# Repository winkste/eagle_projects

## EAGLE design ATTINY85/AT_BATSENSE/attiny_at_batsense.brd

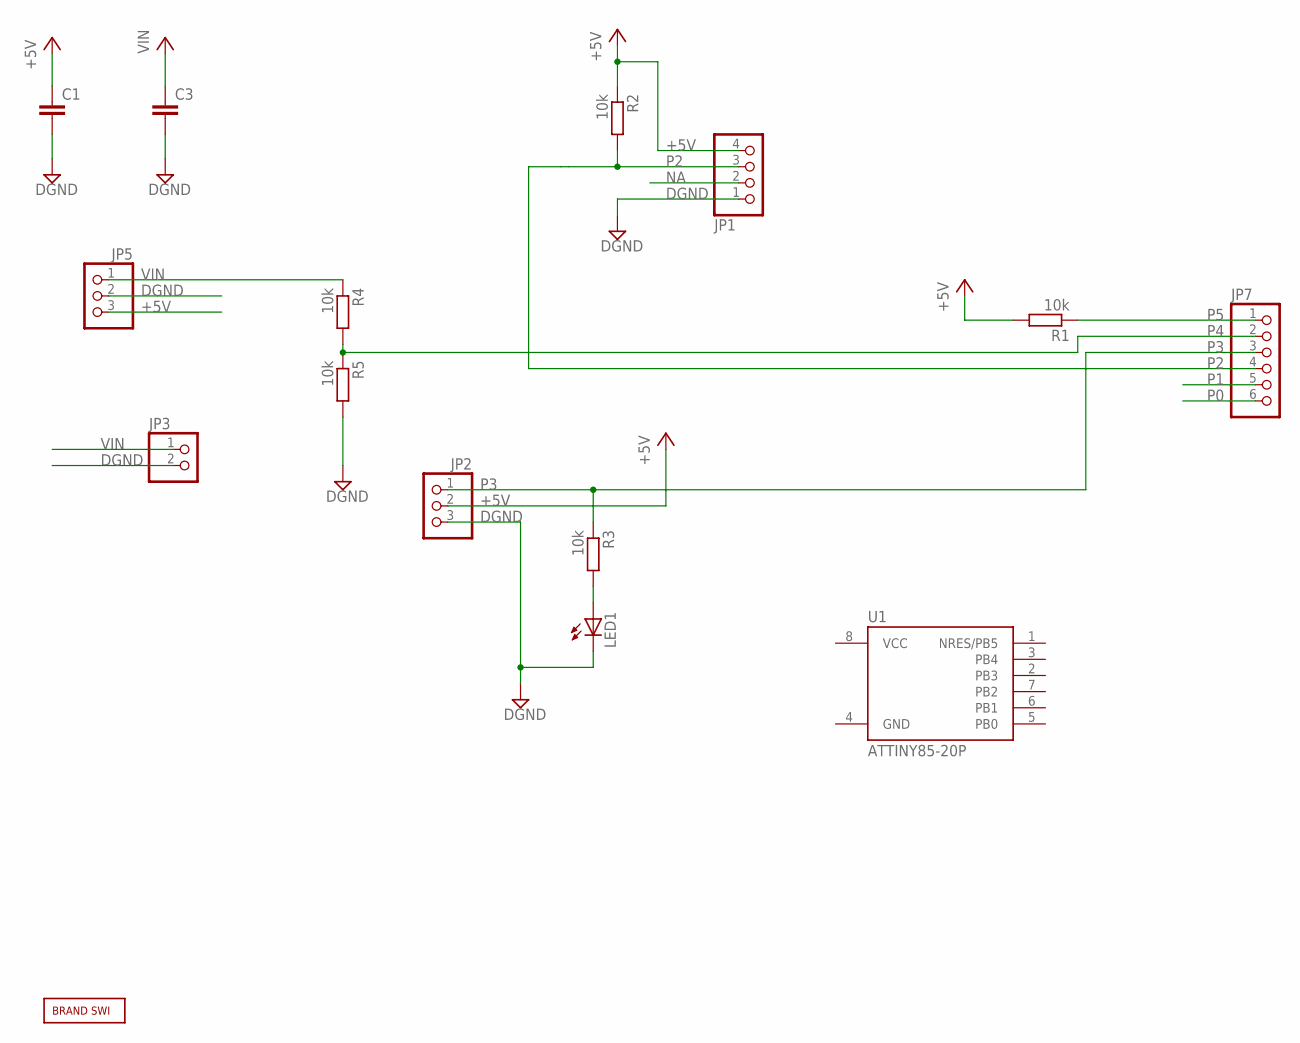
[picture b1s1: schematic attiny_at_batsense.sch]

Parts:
C1, C3: C-EUC1210; C1210
JP1: PINHD-1X4; 1X04
JP2, JP5: PINHD-1X3; 1X03
JP3: PINHD-1X2; 1X02
JP7: PINHD-1X6; 1X06
LED1: LED3MM
R1, R2, R3, R4, R5: 10k; R0805
U1: ATTINY85-20P; PDIP08_300MIL
U$2: BRAND_SWI5X7; BRAND_SWI_5X7

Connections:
+5V: C1.1, JP1.4, JP2.2, JP5.3, R1.2, R2.1
DGND: C1.2, C3.2, JP1.1, JP2.3, JP3.2, JP5.2, LED1.K (C), R5.2
GND: U1.4 (GND)
unnamed: LED1.A, R3.2
NA: JP1.2
P0: JP7.6
P1: JP7.5
P2: JP1.3, JP7.4, R2.2
P3: JP2.1, JP7.3, R3.1
P4: JP7.2, R4.2, R5.1
P5: JP7.1, R1.1
VIN: C3.1, JP3.1, JP5.1, R4.1, U1.8 (VCC)

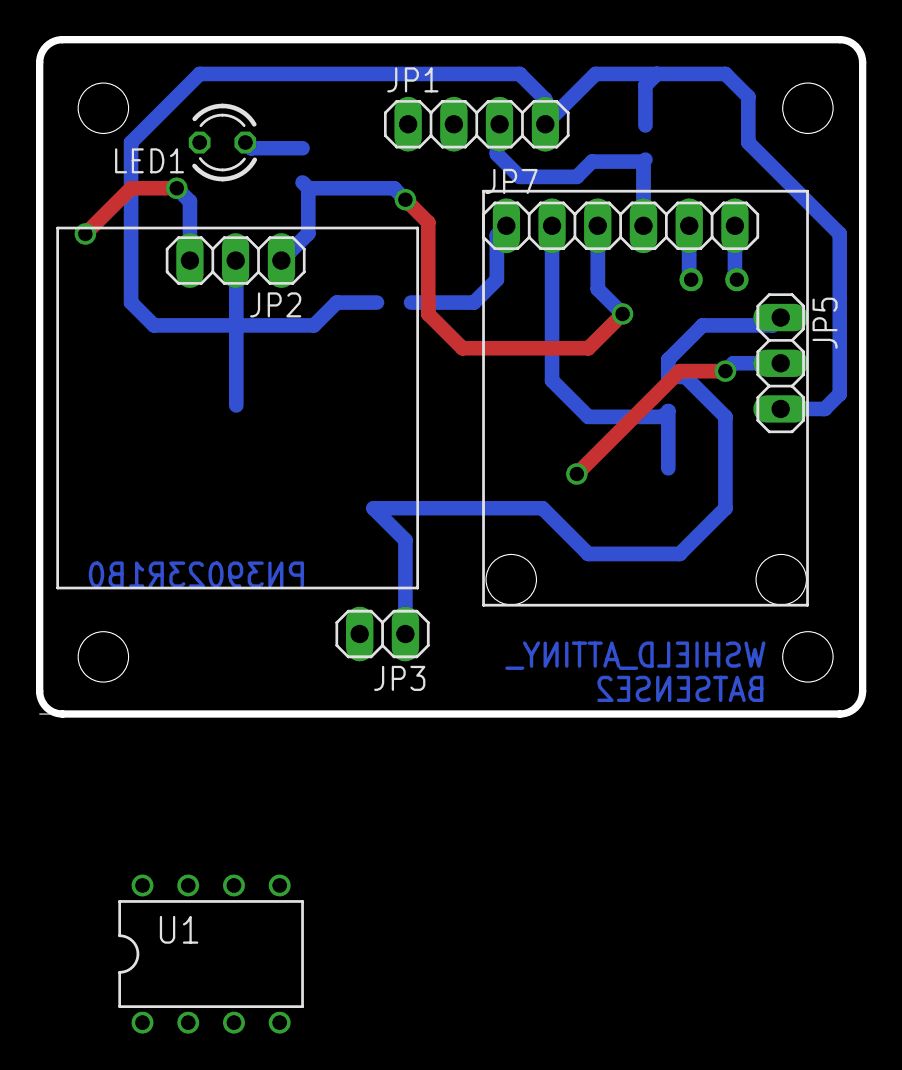
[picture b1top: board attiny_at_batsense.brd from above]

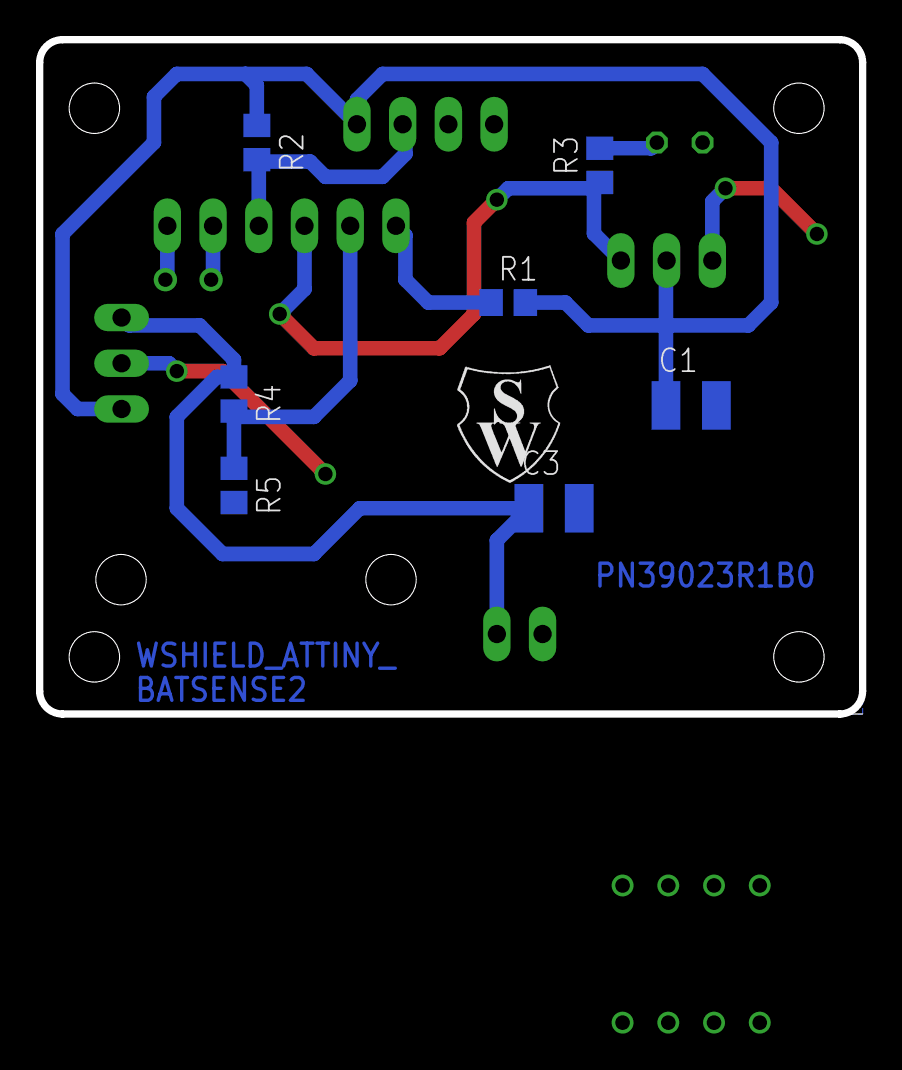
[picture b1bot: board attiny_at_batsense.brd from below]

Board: 2 copper layers, 45.7 x 37.5 mm, 15 parts (8 on the bottom side), 8 nets.

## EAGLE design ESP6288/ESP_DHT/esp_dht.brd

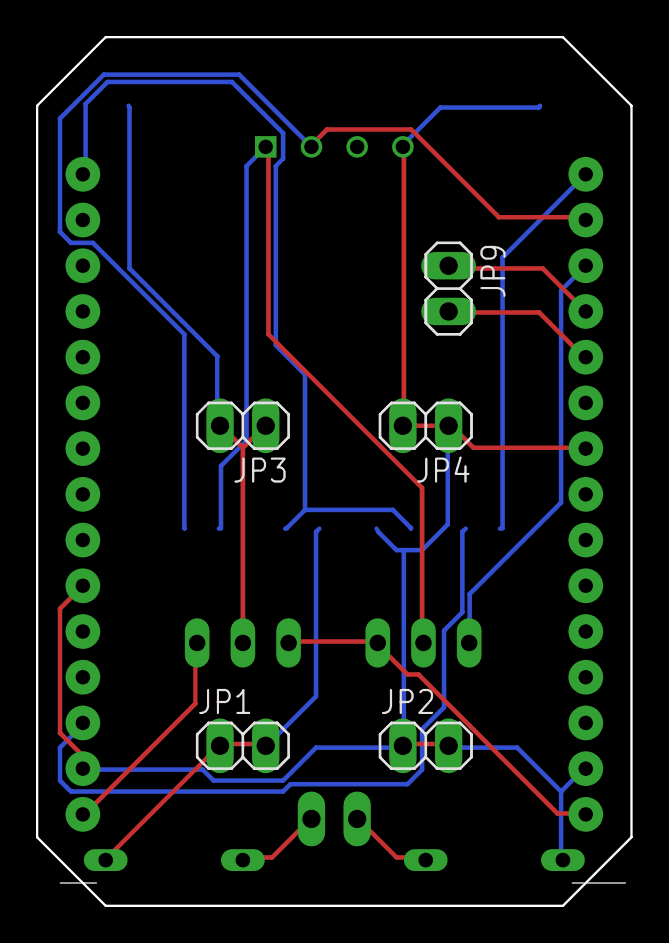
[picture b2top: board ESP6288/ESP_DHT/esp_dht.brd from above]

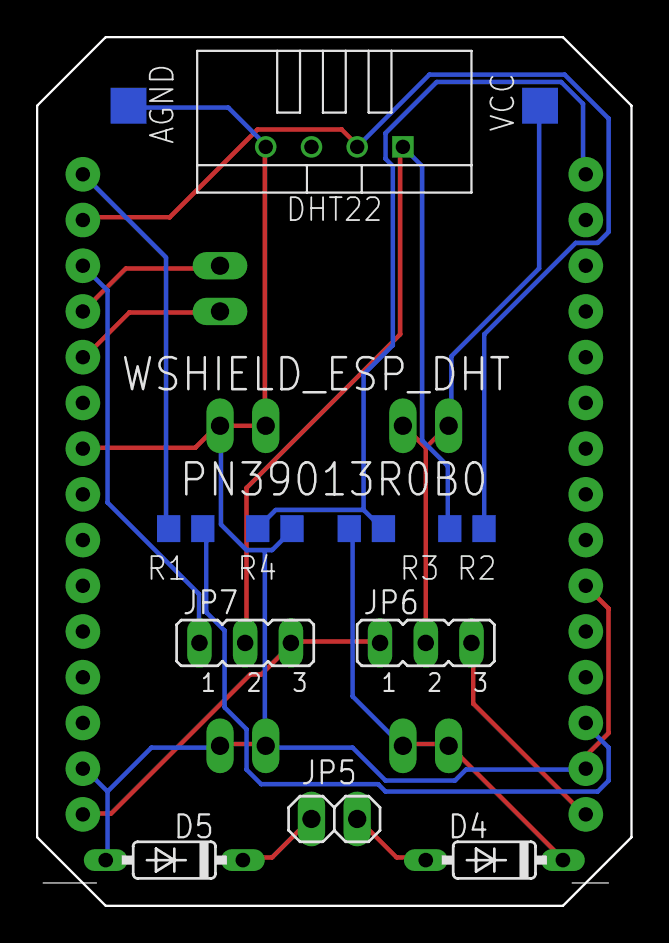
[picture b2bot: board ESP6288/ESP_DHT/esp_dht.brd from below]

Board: 2 copper layers, 33.0 x 48.3 mm, 18 parts (12 on the bottom side), 15 nets.

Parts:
AGND: TPSQTP20SQ; TP20SQ
D4, D5: 1N4148DO35-7; DO35-7
DHT22: TEMP-HUM-SENSOR-DHT22
JP1, JP2, JP3, JP4, JP5, JP9: 1X02
JP6, JP7: JP2
R1: 470Ohm; R0805
R2: 10k; R0805
R3, R4: R0805
U$3: ESP12_DEVKIT
VCC: TPSQTP20SQ; TP20SQ

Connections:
+3V3: JP6.1, JP7.3, U$3.3V3@2
+5V: JP6.3, U$3.5V
+9V: D4.C, JP1.1, JP1.2, R3.1
AGND: AGND.TP, D5.A, DHT22.4, JP2.1, JP2.2, JP4.1, JP4.2, R4.2, U$3.GND@0, U$3.GND@1, U$3.GND@2, U$3.GND@3
DHT_BUS: DHT22.2, R2.2, U$3.D1
DHT_PWR: DHT22.1, JP7.2, R2.1
unnamed: R1.1, U$3.RST
unnamed: R1.2, U$3.D0
unnamed: JP7.1, U$3.D2
unnamed: JP9.2, U$3.D4
unnamed: R3.2, R4.1, U$3.A0
unnamed: JP9.1, U$3.D3
V+: D4.A, JP5.1
V-: D5.C, JP5.2
VCC: JP3.1, JP3.2, JP6.2, VCC.TP

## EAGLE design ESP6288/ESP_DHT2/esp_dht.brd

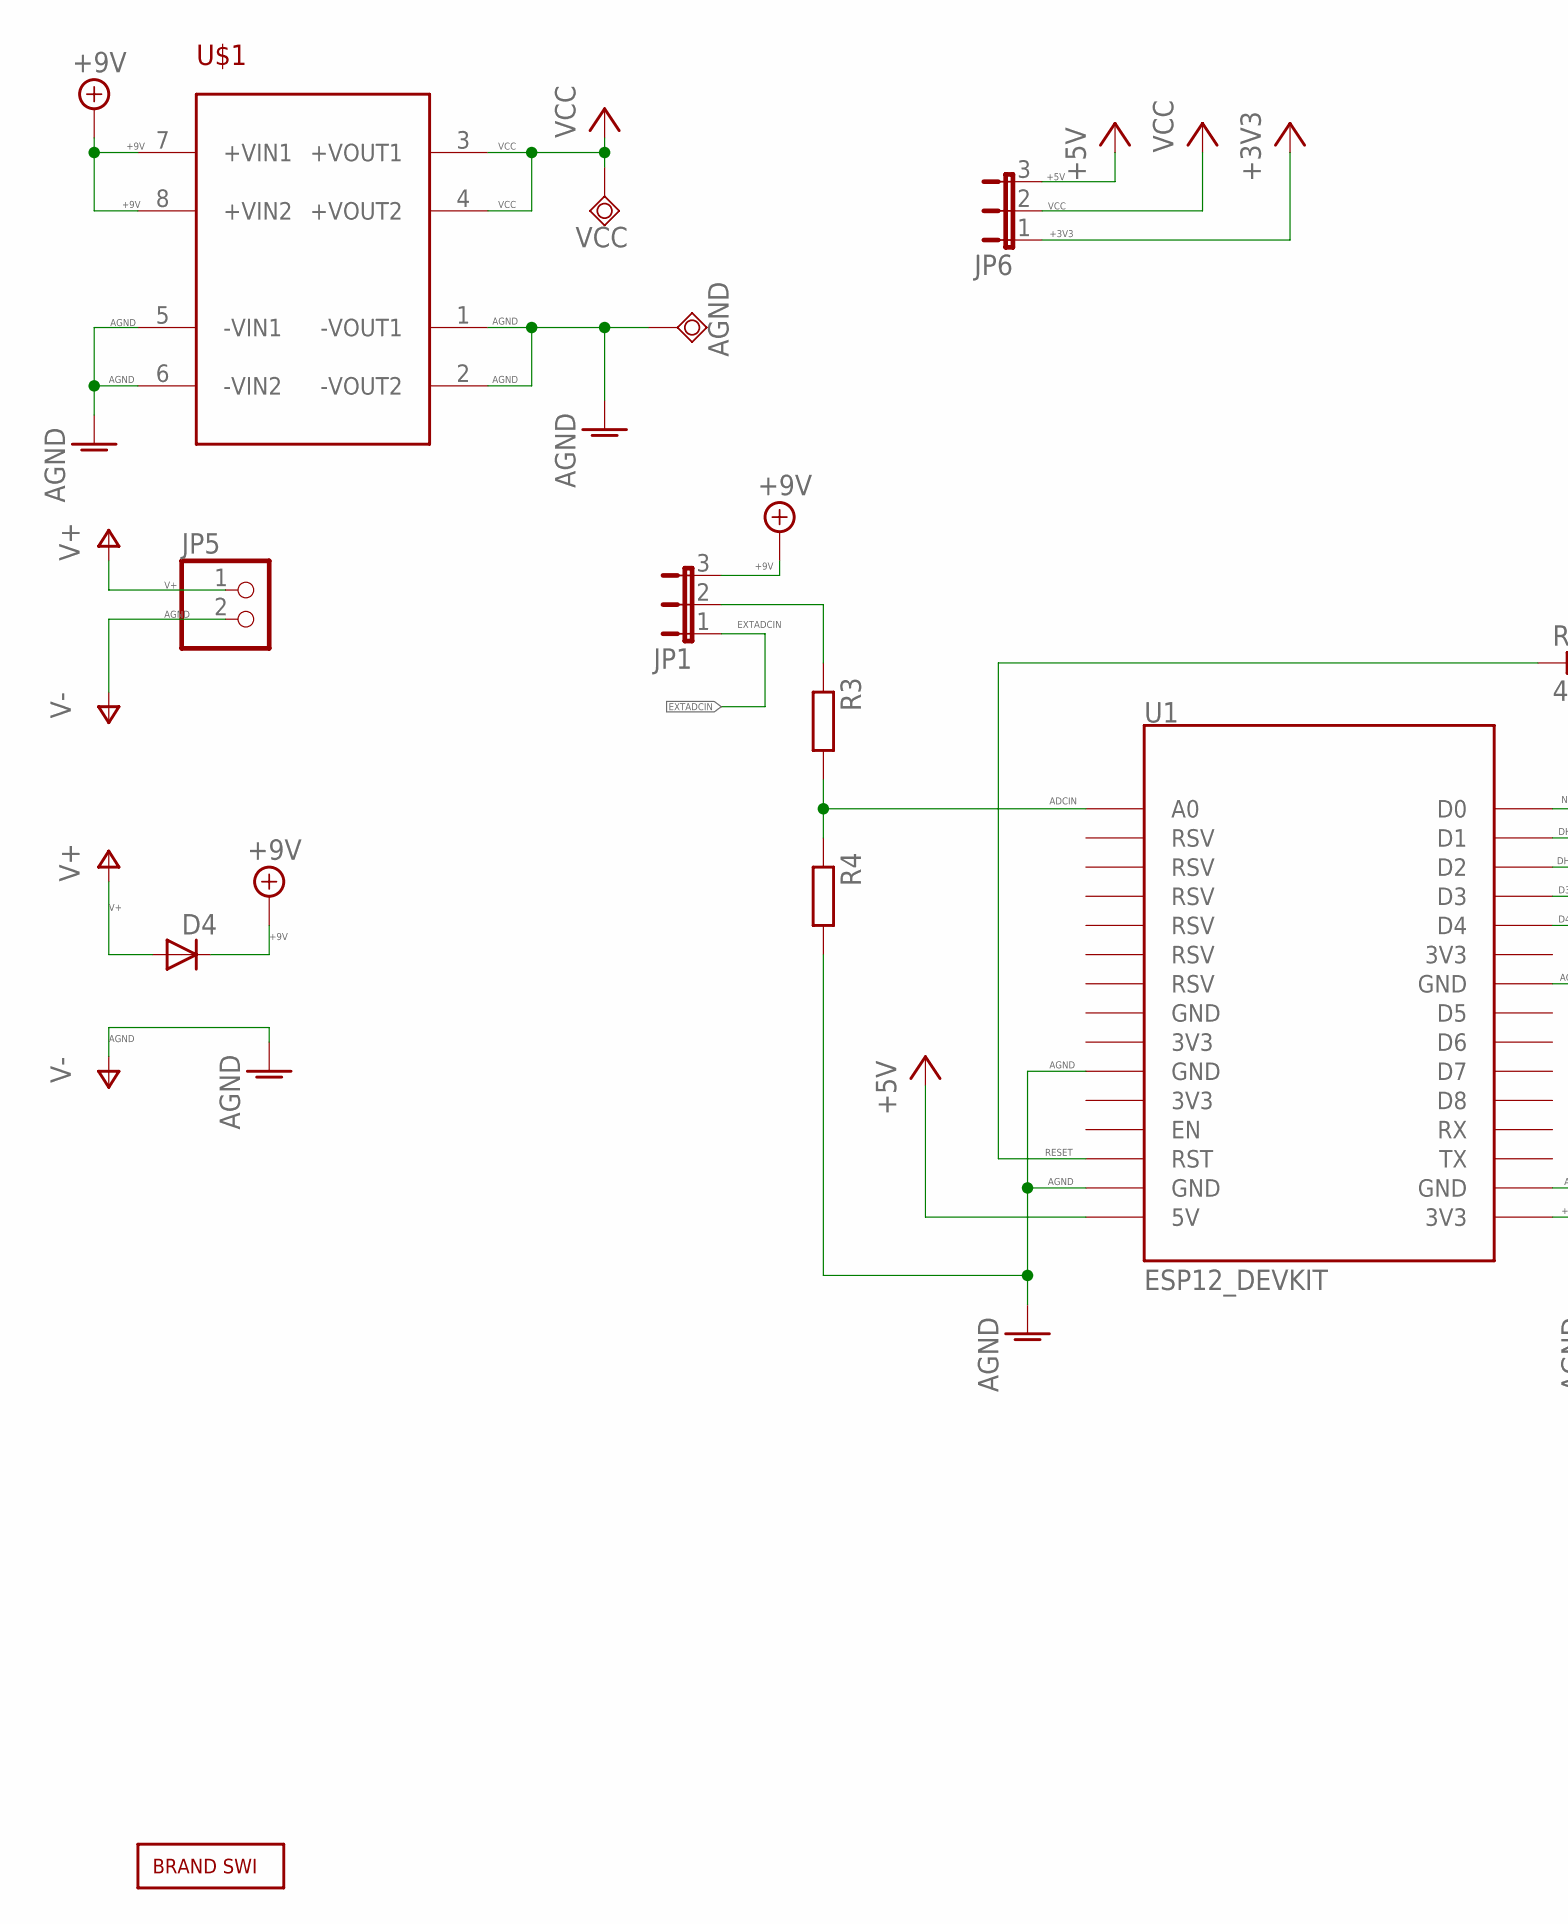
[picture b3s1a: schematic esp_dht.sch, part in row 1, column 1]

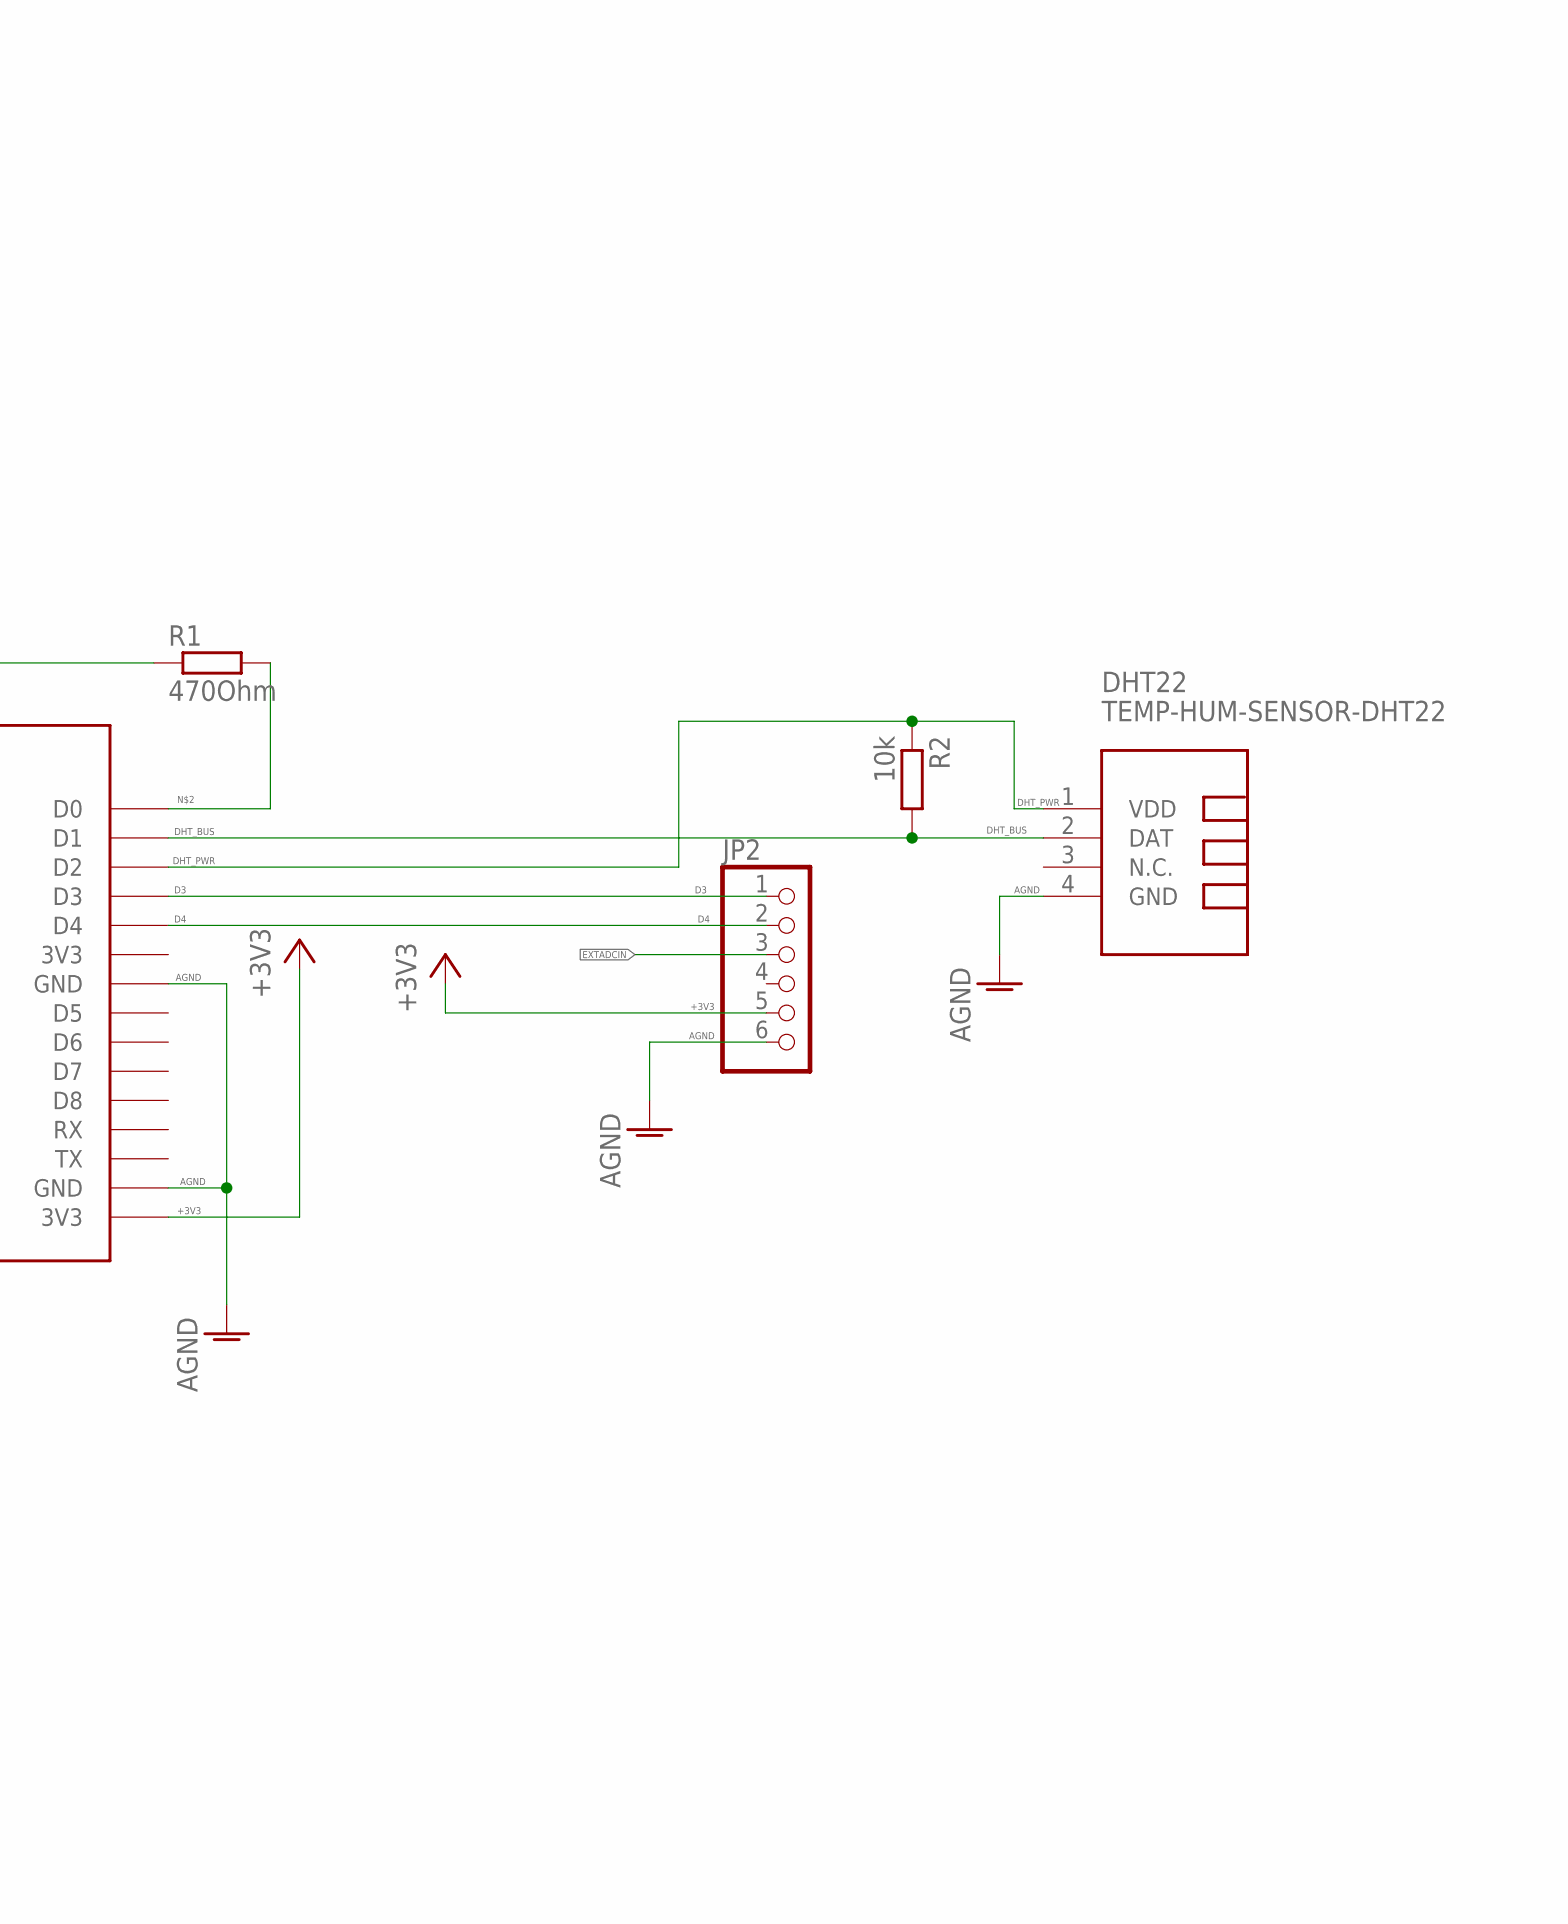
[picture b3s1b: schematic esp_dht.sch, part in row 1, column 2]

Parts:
AGND: TPSQTP20SQ; TP20SQ
D4: 1N4148DO35-7; DO35-7
DHT22: TEMP-HUM-SENSOR-DHT22
JP1, JP6: JP2E; JP2
JP2: PINHD-1X6; 1X06
JP5: PINHD-1X2; 1X02
R1: 470Ohm; R0805
R2: 10k; R0805
R3, R4: R-EU_R0805; R0805
U1: ESP12_DEVKIT
U$1: LVPS
U$2: BRAND_SWI5X7; BRAND_SWI_5X7
VCC: TPSQTP20SQ; TP20SQ

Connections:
+3V3: JP2.5, JP6.1, U1.3V3@2 (3V3)
+5V: JP6.3, U1.5V
+9V: D4.C, JP1.3, U$1.7 (+VIN1), U$1.8 (+VIN2)
ADCIN: R3.2, R4.1, U1.A0
AGND: AGND.TP, DHT22.4 (GND), JP2.6, JP5.2, R4.2, U1.GND@0 (GND), U1.GND@1 (GND), U1.GND@2 (GND), U1.GND@3 (GND), U$1.2 (-VOUT2), U$1.5 (-VIN1), U$1.6 (-VIN2)
D3: JP2.1, U1.D3
D4: JP2.2, U1.D4
DHT_BUS: DHT22.2 (DAT), R2.2, U1.D1
DHT_PWR: DHT22.1 (VDD), R2.1, U1.D2
EXTADCIN: JP1.1, JP2.3
unnamed: JP1.2, R3.1
unnamed: R1.2, U1.D0
RESET: R1.1, U1.RST
V+: D4.A, JP5.1
VCC: JP6.2, U$1.3 (+VOUT1), U$1.4 (+VOUT2), VCC.TP

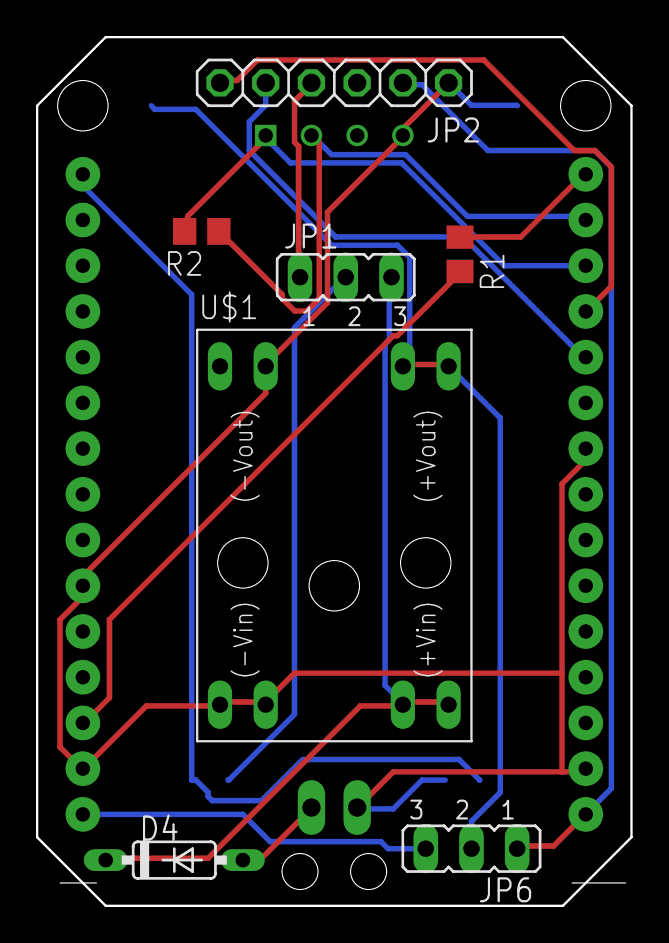
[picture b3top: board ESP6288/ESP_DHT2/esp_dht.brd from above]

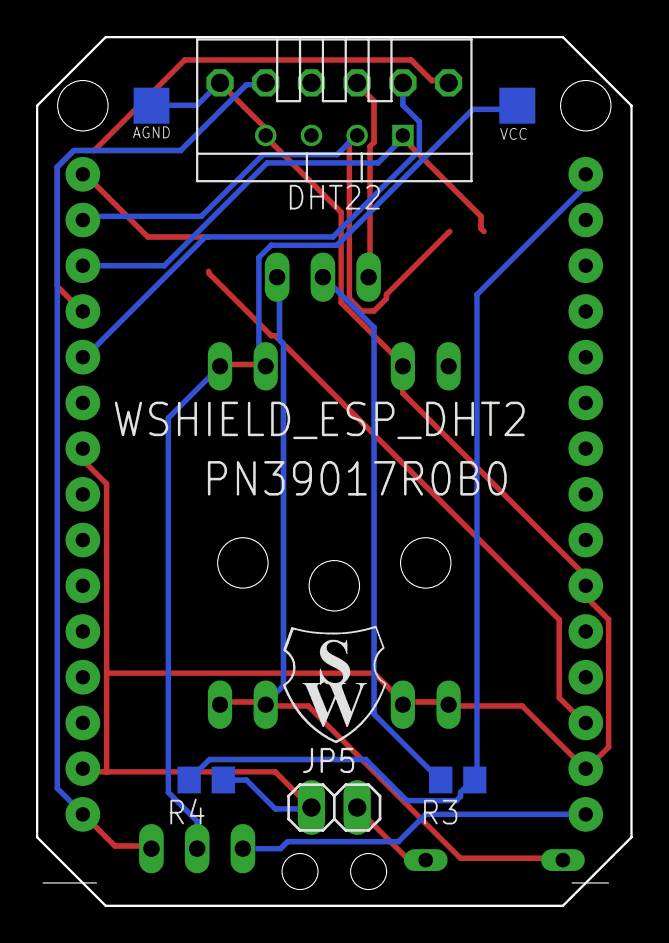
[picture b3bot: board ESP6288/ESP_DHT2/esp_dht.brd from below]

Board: 2 copper layers, 33.0 x 48.3 mm, 15 parts (7 on the bottom side), 15 nets.

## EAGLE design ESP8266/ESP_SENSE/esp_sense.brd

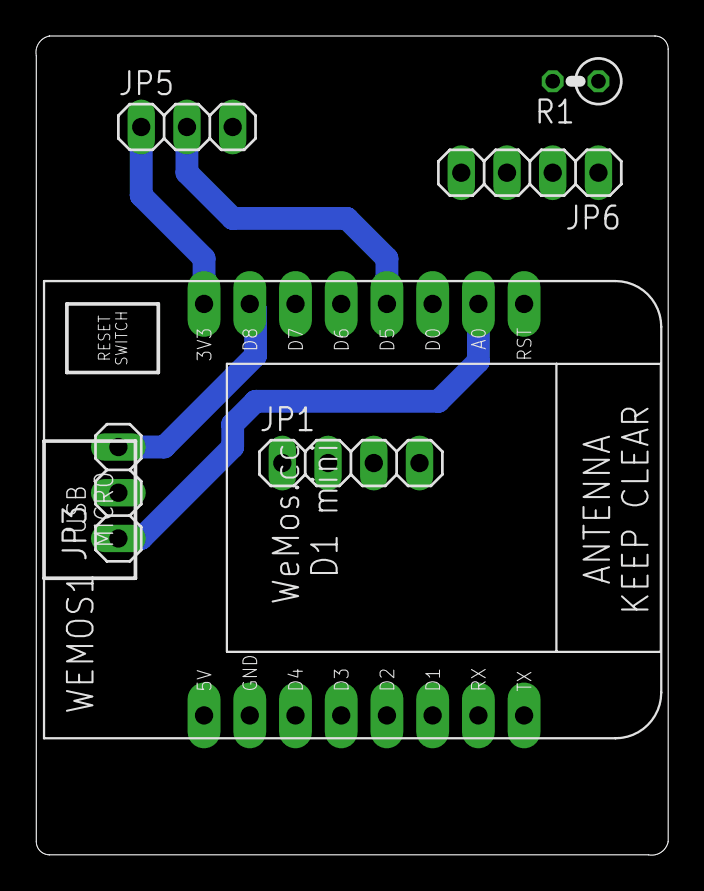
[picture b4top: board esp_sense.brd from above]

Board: 2 copper layers, 35.1 x 45.5 mm, 6 parts (0 on the bottom side), 8 nets.

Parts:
JP1, JP6: 1X04
JP3, JP5: 1X03
R1: 0207/2V
WEMOS1: WEMOS-D1-MINI

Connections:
GND: JP1.4, JP3.2, JP5.3, JP6.4, WEMOS1.GND
unnamed: JP1.1, WEMOS1.5V
unnamed: JP6.2, R1.2, WEMOS1.D3
unnamed: JP3.1, WEMOS1.A0
unnamed: JP5.2, WEMOS1.D5
unnamed: JP6.1, R1.1, WEMOS1.D7
unnamed: JP3.3, WEMOS1.D8
unnamed: JP5.1, WEMOS1.3V3

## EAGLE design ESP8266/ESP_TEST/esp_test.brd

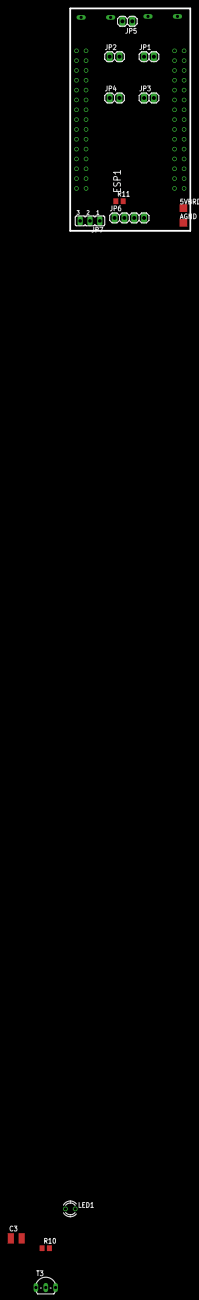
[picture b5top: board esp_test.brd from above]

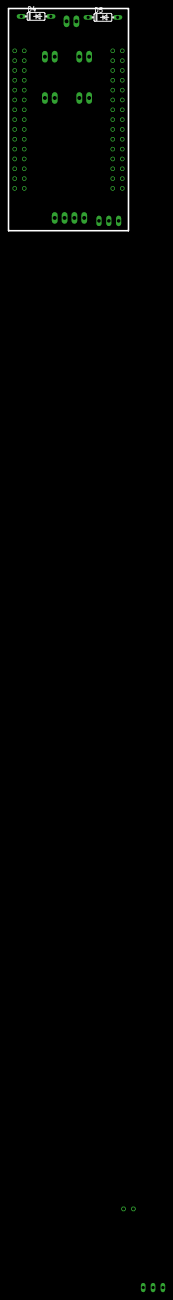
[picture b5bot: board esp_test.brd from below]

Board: 2 copper layers, 31.0 x 57.4 mm, 17 parts (2 on the bottom side), 9 nets, no tracks yet.

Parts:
5VBRD: TPSQTP20SQ; TP20SQ
AGND: TPSQTP20SQ; TP20SQ
C3: C1210
D4, D5: 1N4148DO35-7; DO35-7
ESP1: ESP12E_DEVKIT
JP1, JP2, JP3, JP4, JP5: 1X02
JP6: 1X04
JP7: JP2
LED1: LED3MM
R10: 2k; R0805
R11: R0805
T3: TO92-CBE

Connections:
+5V: 5VBRD.TP, ESP1.VIN, ESP1.VIN1, JP3.1, JP3.2, JP7.1
+9V: D4.C, JP1.1, JP1.2
AGND: AGND.TP, D5.A, ESP1.GND@0, ESP1.GND@1, ESP1.GND@2, ESP1.GND@3, ESP1.GND@4, ESP1.GND@5, ESP1.GND@6, ESP1.GND@7, JP2.1, JP2.2, JP4.1, JP4.2, JP6.4
DHT_BUS: ESP1.D4, ESP1.D41, JP6.2, R11.2
DHT_PWR: JP6.1, JP7.2, R11.1
ESP3V3: ESP1.3V3@2, JP7.3
unnamed: LED1.A, R10.2
V+: D4.A, JP5.1
V-: D5.C, JP5.2

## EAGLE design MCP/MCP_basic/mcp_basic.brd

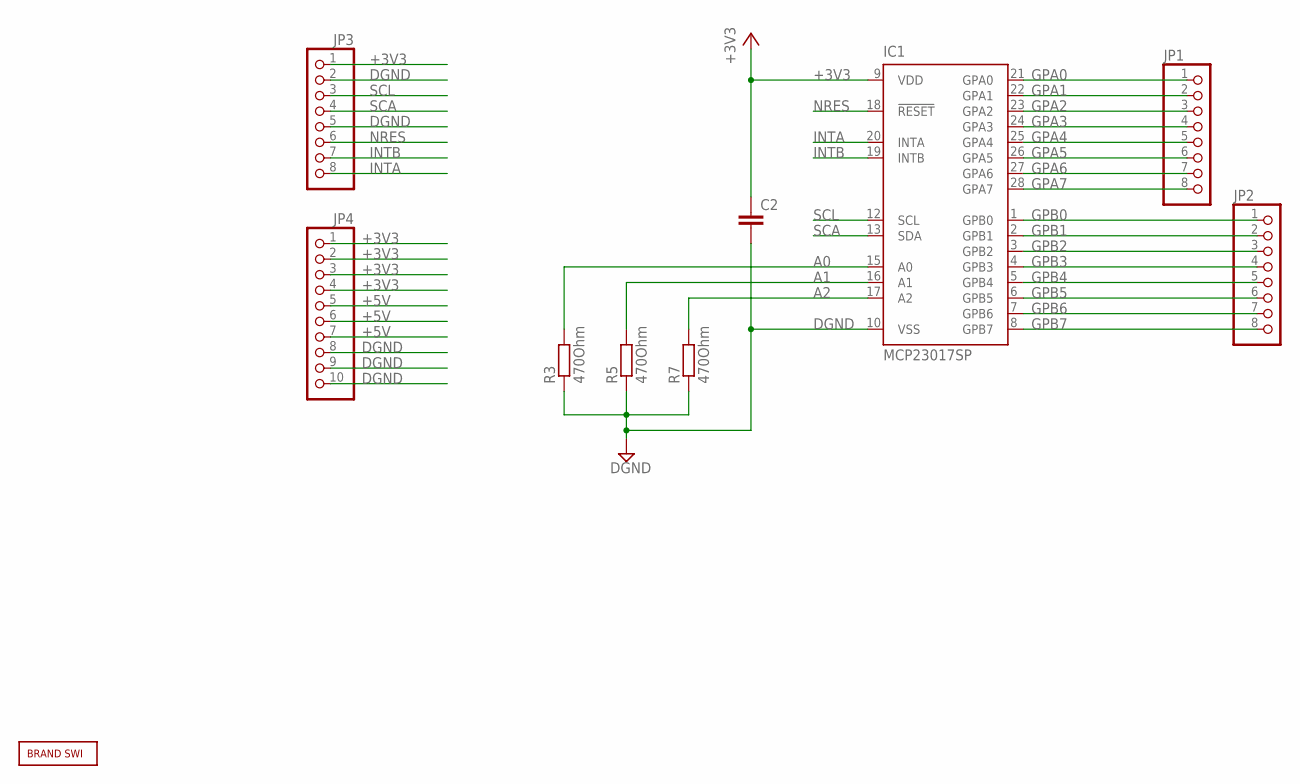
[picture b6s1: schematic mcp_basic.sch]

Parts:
C2: C-EUC1210; C1210
IC1: MCP23017SP; DIL28-3
JP1, JP2, JP3: PINHD-1X8; 1X08
JP4: PINHD-1X10; 1X10
R3, R5, R7: 470Ohm; R0805
U$2: BRAND_SWI5X7; BRAND_SWI_5X7

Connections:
+3V3: C2.1, IC1.9 (VDD), JP3.1, JP4.1, JP4.2, JP4.3, JP4.4
+5V: JP4.5, JP4.6, JP4.7
A0: IC1.15 (A0), R3.2
A1: IC1.16 (A1), R5.2
A2: IC1.17 (A2), R7.2
DGND: C2.2, IC1.10 (VSS), JP3.2, JP3.5, JP4.8, JP4.9, JP4.10, R3.1, R5.1, R7.1
GPA0: IC1.21 (GPA0), JP1.1
GPA1: IC1.22 (GPA1), JP1.2
GPA2: IC1.23 (GPA2), JP1.3
GPA3: IC1.24 (GPA3), JP1.4
GPA4: IC1.25 (GPA4), JP1.5
GPA5: IC1.26 (GPA5), JP1.6
GPA6: IC1.27 (GPA6), JP1.7
GPA7: IC1.28 (GPA7), JP1.8
GPB0: IC1.1 (GPB0), JP2.1
GPB1: IC1.2 (GPB1), JP2.2
GPB2: IC1.3 (GPB2), JP2.3
GPB3: IC1.4 (GPB3), JP2.4
GPB4: IC1.5 (GPB4), JP2.5
GPB5: IC1.6 (GPB5), JP2.6
GPB6: IC1.7 (GPB6), JP2.7
GPB7: IC1.8 (GPB7), JP2.8
INTA: IC1.20 (INTA), JP3.8
INTB: IC1.19 (INTB), JP3.7
NRES: IC1.18 (!RESET), JP3.6
SCA: IC1.13 (SDA), JP3.4
SCL: IC1.12 (SCL), JP3.3

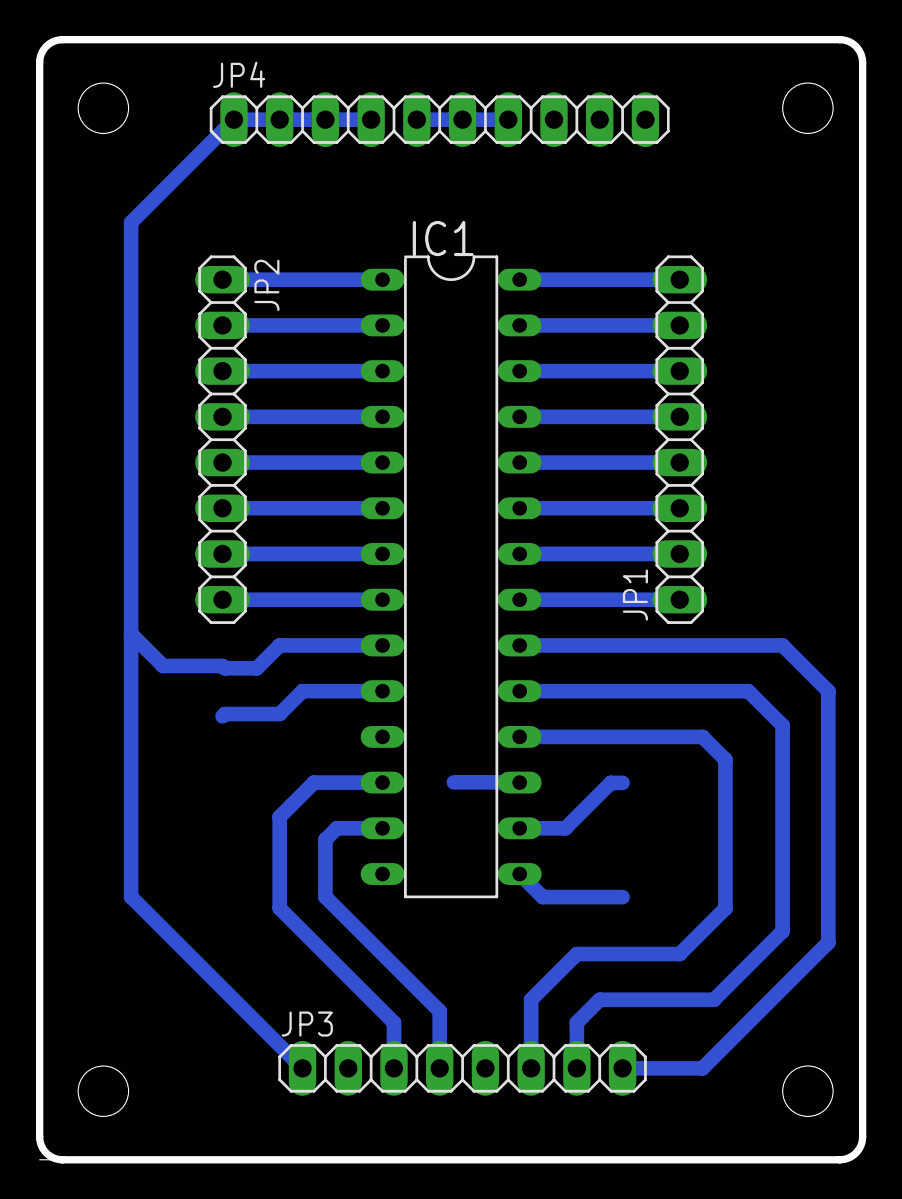
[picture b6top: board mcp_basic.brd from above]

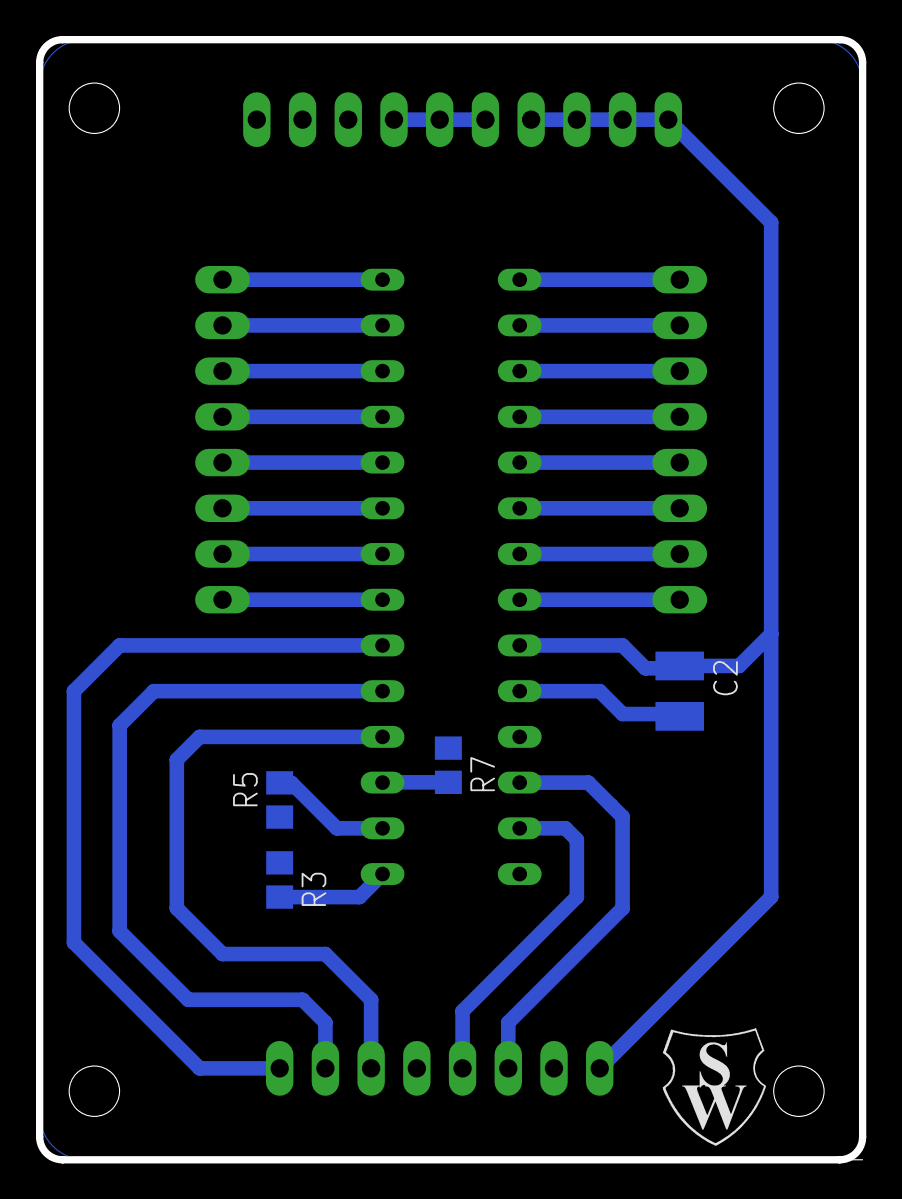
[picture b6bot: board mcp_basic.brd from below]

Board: 2 copper layers, 45.7 x 62.2 mm, 10 parts (5 on the bottom side), 27 nets.

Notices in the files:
parts and their libraries:
diy-modules: Released under the Creative Commons Attribution 4.0 International License: http://creativecommons.org/licenses/by/4.0
